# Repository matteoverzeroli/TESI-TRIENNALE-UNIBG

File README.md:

# Progetto di un sistema optoelettronico indossabile per misure fotopletismografiche (Design of a wearable optoelectronic system for photoplethysmographic measurements)
Progetto di tesi triennale presso il laboratorio di Microelettronica dell'Università degli Studi di Bergamo

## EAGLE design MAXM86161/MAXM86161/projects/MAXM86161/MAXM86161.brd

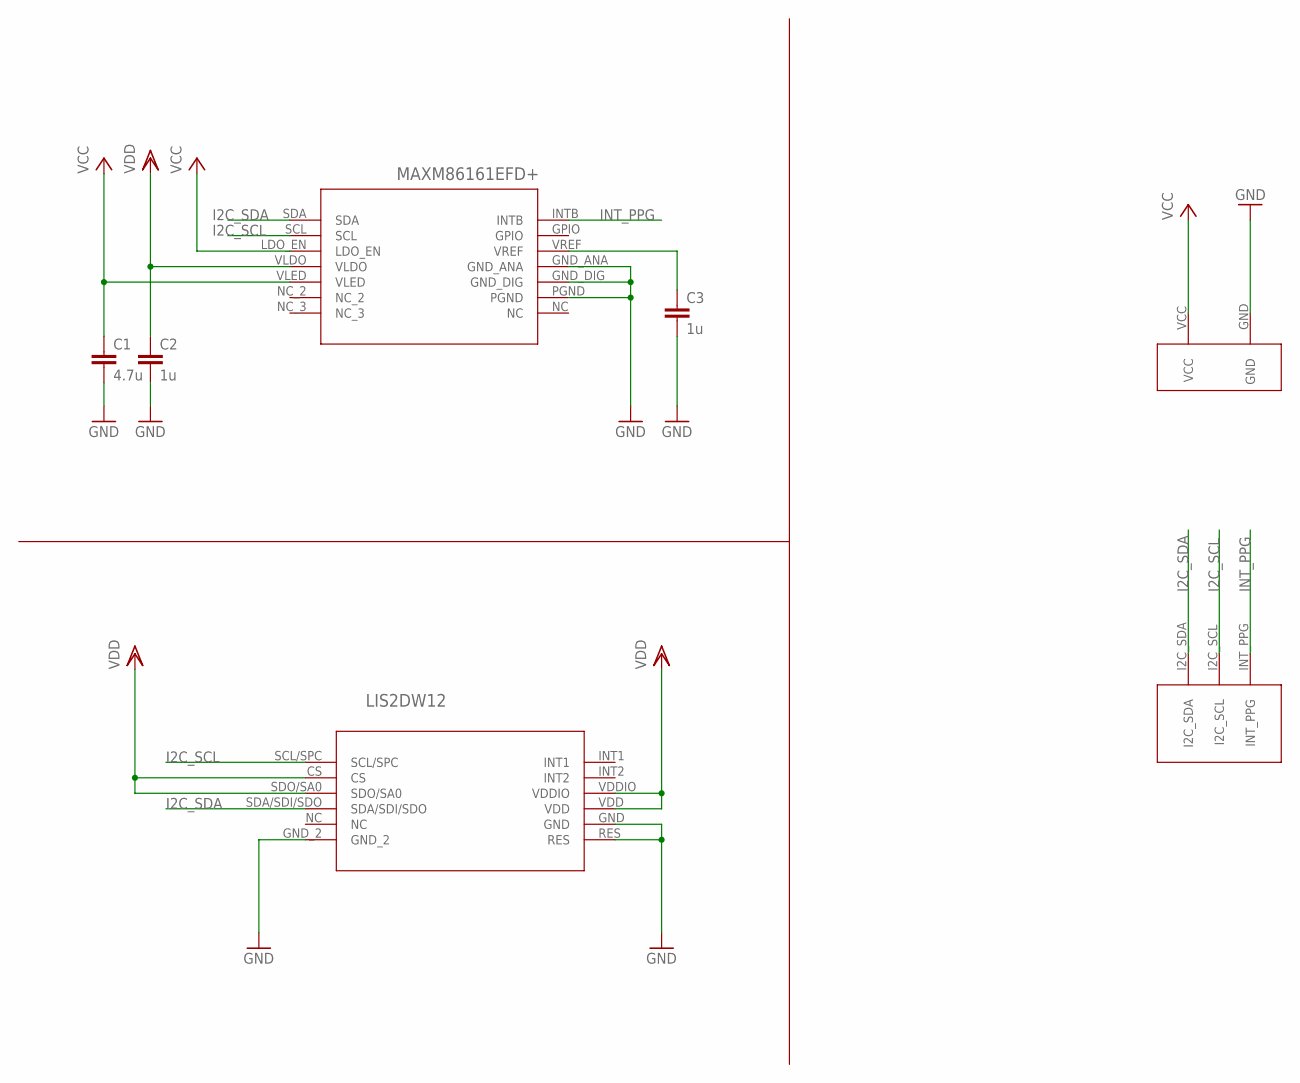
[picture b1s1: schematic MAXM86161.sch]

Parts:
C1: 4.7u; C0603
C2, C3: 1u; C0402
U1: MAXM86161EFD+; 21-100309A_MXM
U2: LIS2DW12; LIS2DW12_LGA-12_2X2X0P7_STM
U$1: PAD_2
U$2: PAD_3

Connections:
GND: C1.P$2 (2), C2.P$2 (2), C3.P$2 (2), U1.GND_ANA, U1.GND_DIG, U1.PGND, U2.GND, U2.GND_2, U2.RES, U$1.GND
I2C_SCL: U1.SCL, U2.SCL/SPC, U$2.I2C_SCL
I2C_SDA: U1.SDA, U2.SDA/SDI/SDO, U$2.I2C_SDA
INT_PPG: U1.INTB, U$2.INT_PPG
unnamed: C3.P$1 (1), U1.VREF
VCC: C1.P$1 (1), U1.LDO_EN, U1.VLED, U$1.VCC
VDD: C2.P$1 (1), U1.VLDO, U2.CS, U2.SDO/SA0, U2.VDD, U2.VDDIO

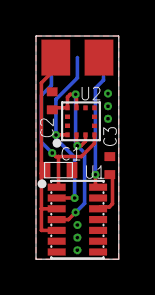
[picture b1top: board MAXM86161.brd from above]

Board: 2 copper layers, 4.6 x 12.4 mm, 7 parts (1 on the bottom side), 7 nets.

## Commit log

2021-09-16 added eagle file source
2023-04-20 Create licence

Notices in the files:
parts and their libraries:
COPYRIGHT: Copyright (C) 2018 Accelerated Designs. All rights reserved
